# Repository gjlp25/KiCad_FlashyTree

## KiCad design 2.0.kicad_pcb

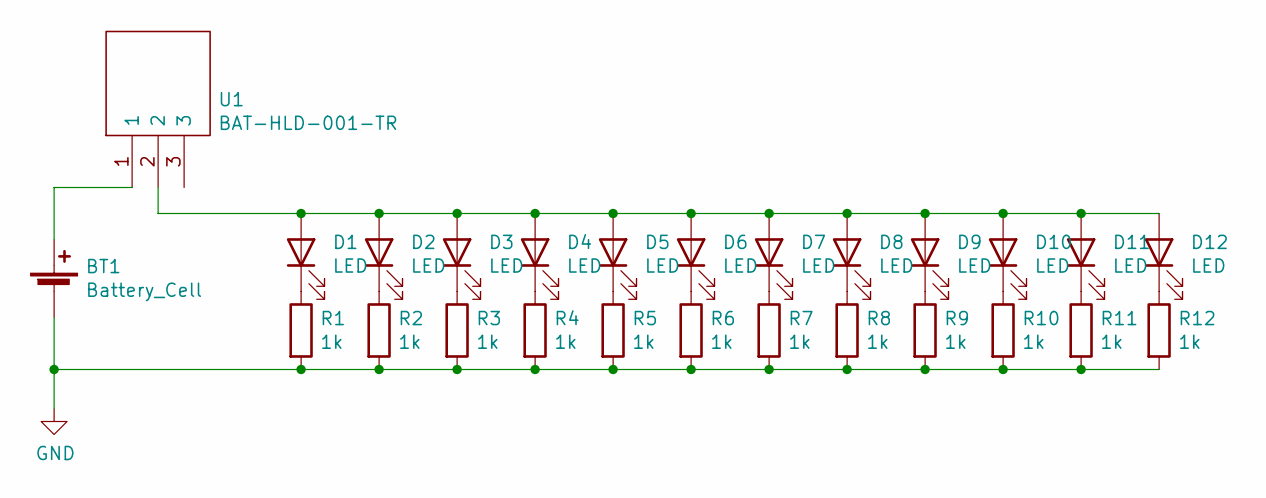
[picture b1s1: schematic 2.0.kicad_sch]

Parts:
BT1: Battery_Cell; BC2001
D1, D2, D3, D4, D5, D6, D7, D8, D9, D10, D11, D12: LED; LED_0805_2012Metric_Pad1.15x1.40mm_HandSolder
R1, R2, R3, R4, R5, R6, R7, R8, R9, R10, R11, R12: 1k; R_0805_2012Metric_Pad1.20x1.40mm_HandSolder
U1: BAT-HLD-001-TR; BATHLD001TR; Manufacturer_Part_Number BAT-HLD-001-TR; Mouser Part Number 712-BAT-HLD-001-TR

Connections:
GND: BT1.2 (-), R1.2, R2.2, R3.2, R4.2, R5.2, R6.2, R7.2, R8.2, R9.2, R10.2, R11.2, R12.2
unnamed 1: BT1.1 (+), U1.1; also elsewhere on the board
unnamed: D1.1 (K), R1.1
unnamed 3: D1.2 (A), D2.2 (A), D3.2 (A), D4.2 (A), D5.2 (A), D6.2 (A), D7.2 (A), D8.2 (A), D9.2 (A), D10.2 (A), D11.2 (A), D12.2 (A), U1.2; also elsewhere on the board
unnamed: D2.1 (K), R2.1
unnamed: D3.1 (K), R3.1
unnamed: D4.1 (K), R4.1
unnamed: D5.1 (K), R5.1
unnamed: D6.1 (K), R6.1
unnamed: D7.1 (K), R7.1
unnamed: D8.1 (K), R8.1
unnamed: D9.1 (K), R9.1
unnamed: D10.1 (K), R10.1
unnamed: D11.1 (K), R11.1
unnamed: D12.1 (K), R12.1

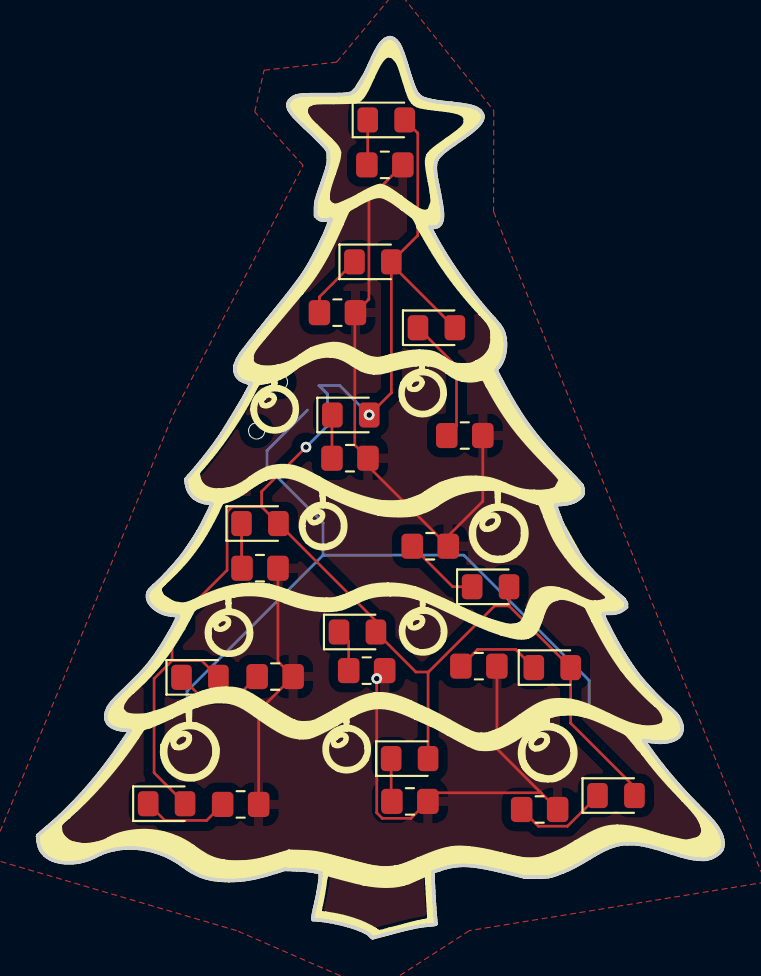
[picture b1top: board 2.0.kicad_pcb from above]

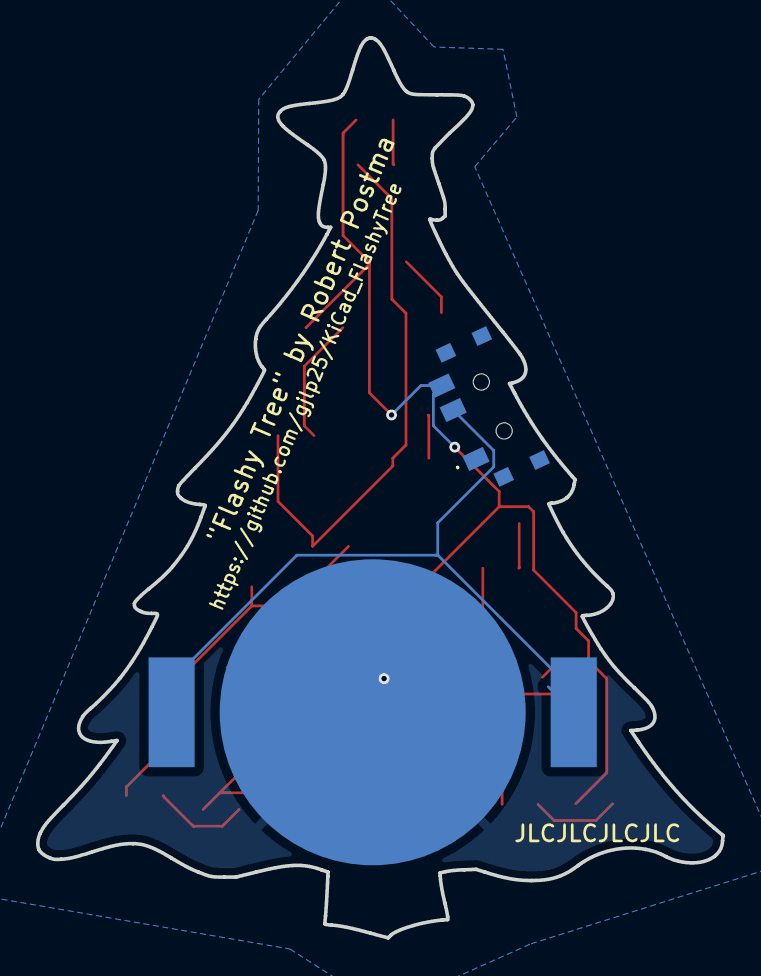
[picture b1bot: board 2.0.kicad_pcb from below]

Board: 2 copper layers, 38.1 x 50.0 mm, 26 parts (2 on the bottom side), 15 nets.

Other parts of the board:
J1: MK-12C02; MK12C02

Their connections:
unnamed 1: J1.2 (COM); also elsewhere on the board
unnamed 3: J1.3 (NO); also elsewhere on the board

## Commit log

2022-10-06 Added OSHW logo
2022-10-06 Minor copper changes
2022-10-06 Added gerbers and BOM
2022-10-07 Added renders
2022-10-07 Added gerbers and renders
2022-11-02 Fixed PCB
2022-11-22 Fixed position ordernr
2023-01-23 new gerbers
